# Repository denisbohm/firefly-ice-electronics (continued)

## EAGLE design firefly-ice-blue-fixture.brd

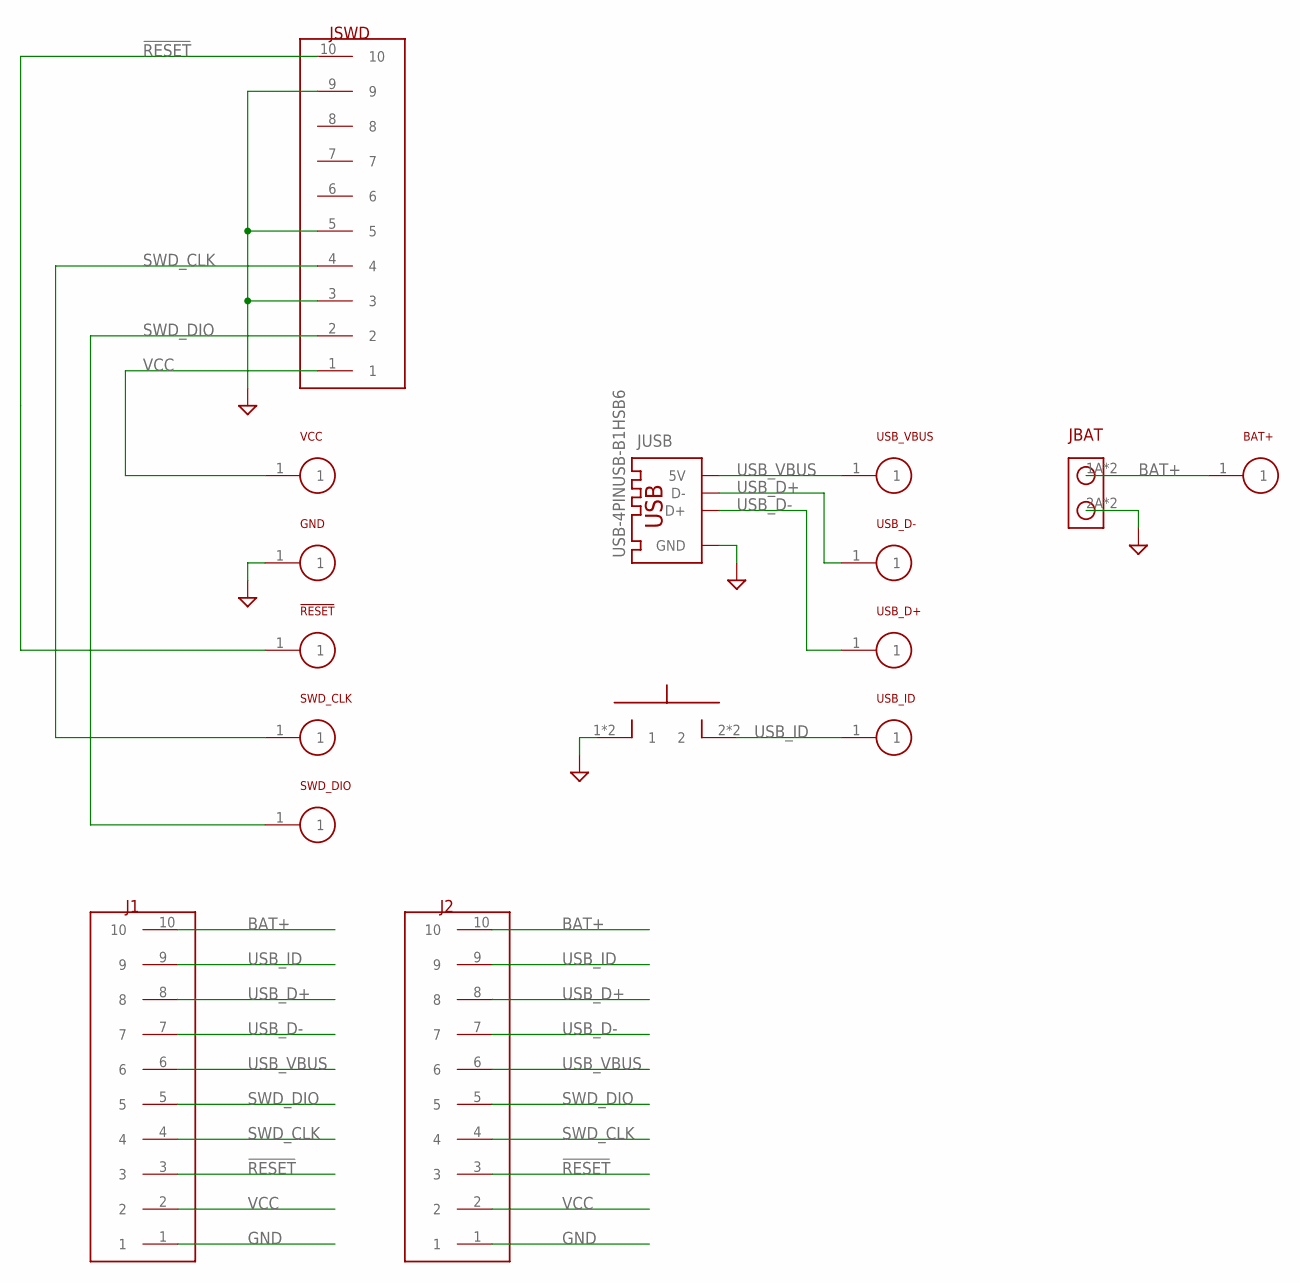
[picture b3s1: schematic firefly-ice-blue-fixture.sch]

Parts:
!RESET: TARGET-PINPROBE-0985; PROBE-0985
BAT+: TARGET-PINPROBE-0985; PROBE-0985
GND: TARGET-PINPROBE-0985; PROBE-0985
J1, J2: CON-10; CON-HEADER-10
JBAT: CON-220020303-D021B01LF; 20020303-D021B01LF
JSWD: CON-10SWD; SWD-10
JUSB: USB-4PINUSB-B1HSB6; USB-B1HSB6
SRES: SPST-NOKS-01Q-01; KS-01Q-01
SWD_CLK: TARGET-PINPROBE-0985; PROBE-0985
SWD_DIO: TARGET-PINPROBE-0985; PROBE-0985
USB_D+: TARGET-PINPROBE-0985; PROBE-0985
USB_D-: TARGET-PINPROBE-0985; PROBE-0985
USB_ID: TARGET-PINPROBE-0985; PROBE-0985
USB_VBUS: TARGET-PINPROBE-0985; PROBE-0985
VCC: TARGET-PINPROBE-0985; PROBE-0985

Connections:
!RESET: !RESET.1, J1.3, J2.3, JSWD.10
BAT+: BAT+.1, J1.10, J2.10, JBAT.1A (1), JBAT.1B (1)
GND: GND.1, J1.1, J2.1, JBAT.2A (2), JBAT.2B (2), JSWD.3, JSWD.5, JSWD.9, JUSB.4 (GND), SRES.1, SRES.3 (1)
SWD_CLK: J1.4, J2.4, JSWD.4, SWD_CLK.1
SWD_DIO: J1.5, J2.5, JSWD.2, SWD_DIO.1
USB_D+: J1.8, J2.8, JUSB.2 (D-), USB_D-.1
USB_D-: J1.7, J2.7, JUSB.3 (D+), USB_D+.1
USB_ID: J1.9, J2.9, SRES.2, SRES.4 (2), USB_ID.1
USB_VBUS: J1.6, J2.6, JUSB.1 (5V), USB_VBUS.1
VCC: J1.2, J2.2, JSWD.1, VCC.1

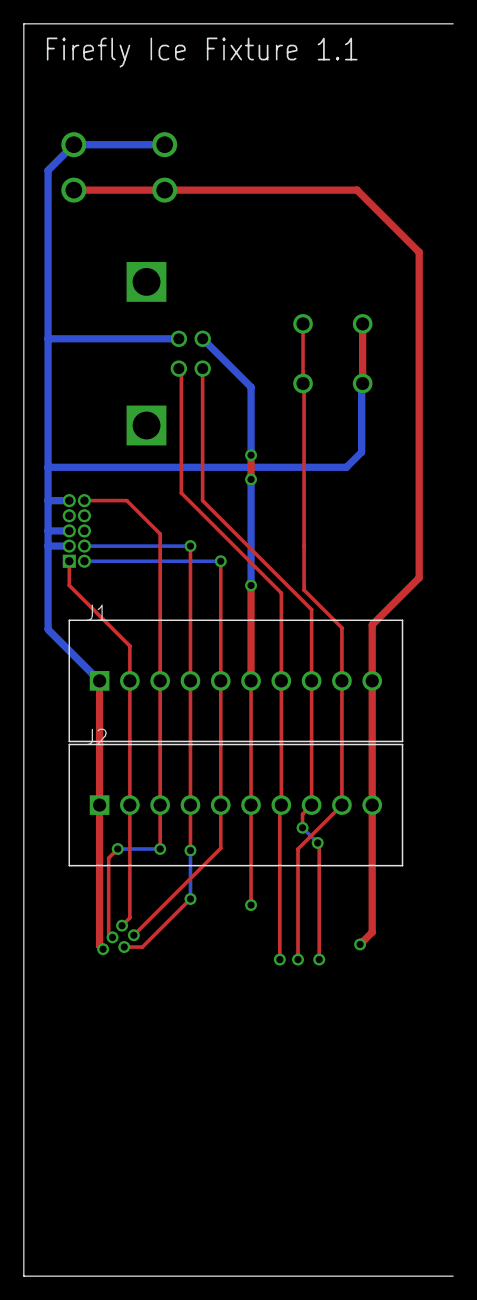
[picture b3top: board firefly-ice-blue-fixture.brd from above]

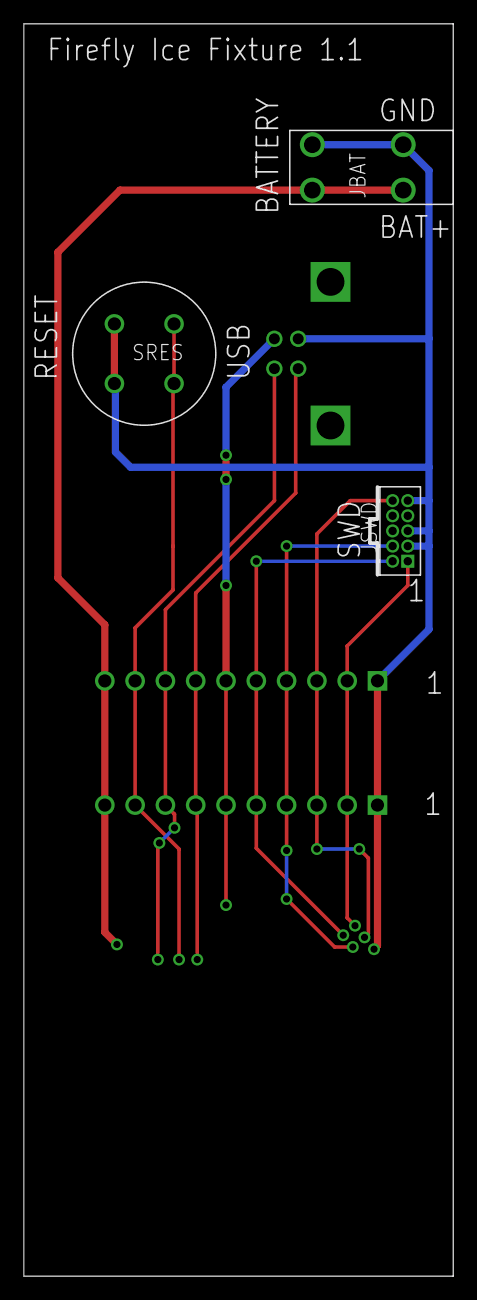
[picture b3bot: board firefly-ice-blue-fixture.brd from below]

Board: 2 copper layers, 36.0 x 105.0 mm, 16 parts (4 on the bottom side), 10 nets.

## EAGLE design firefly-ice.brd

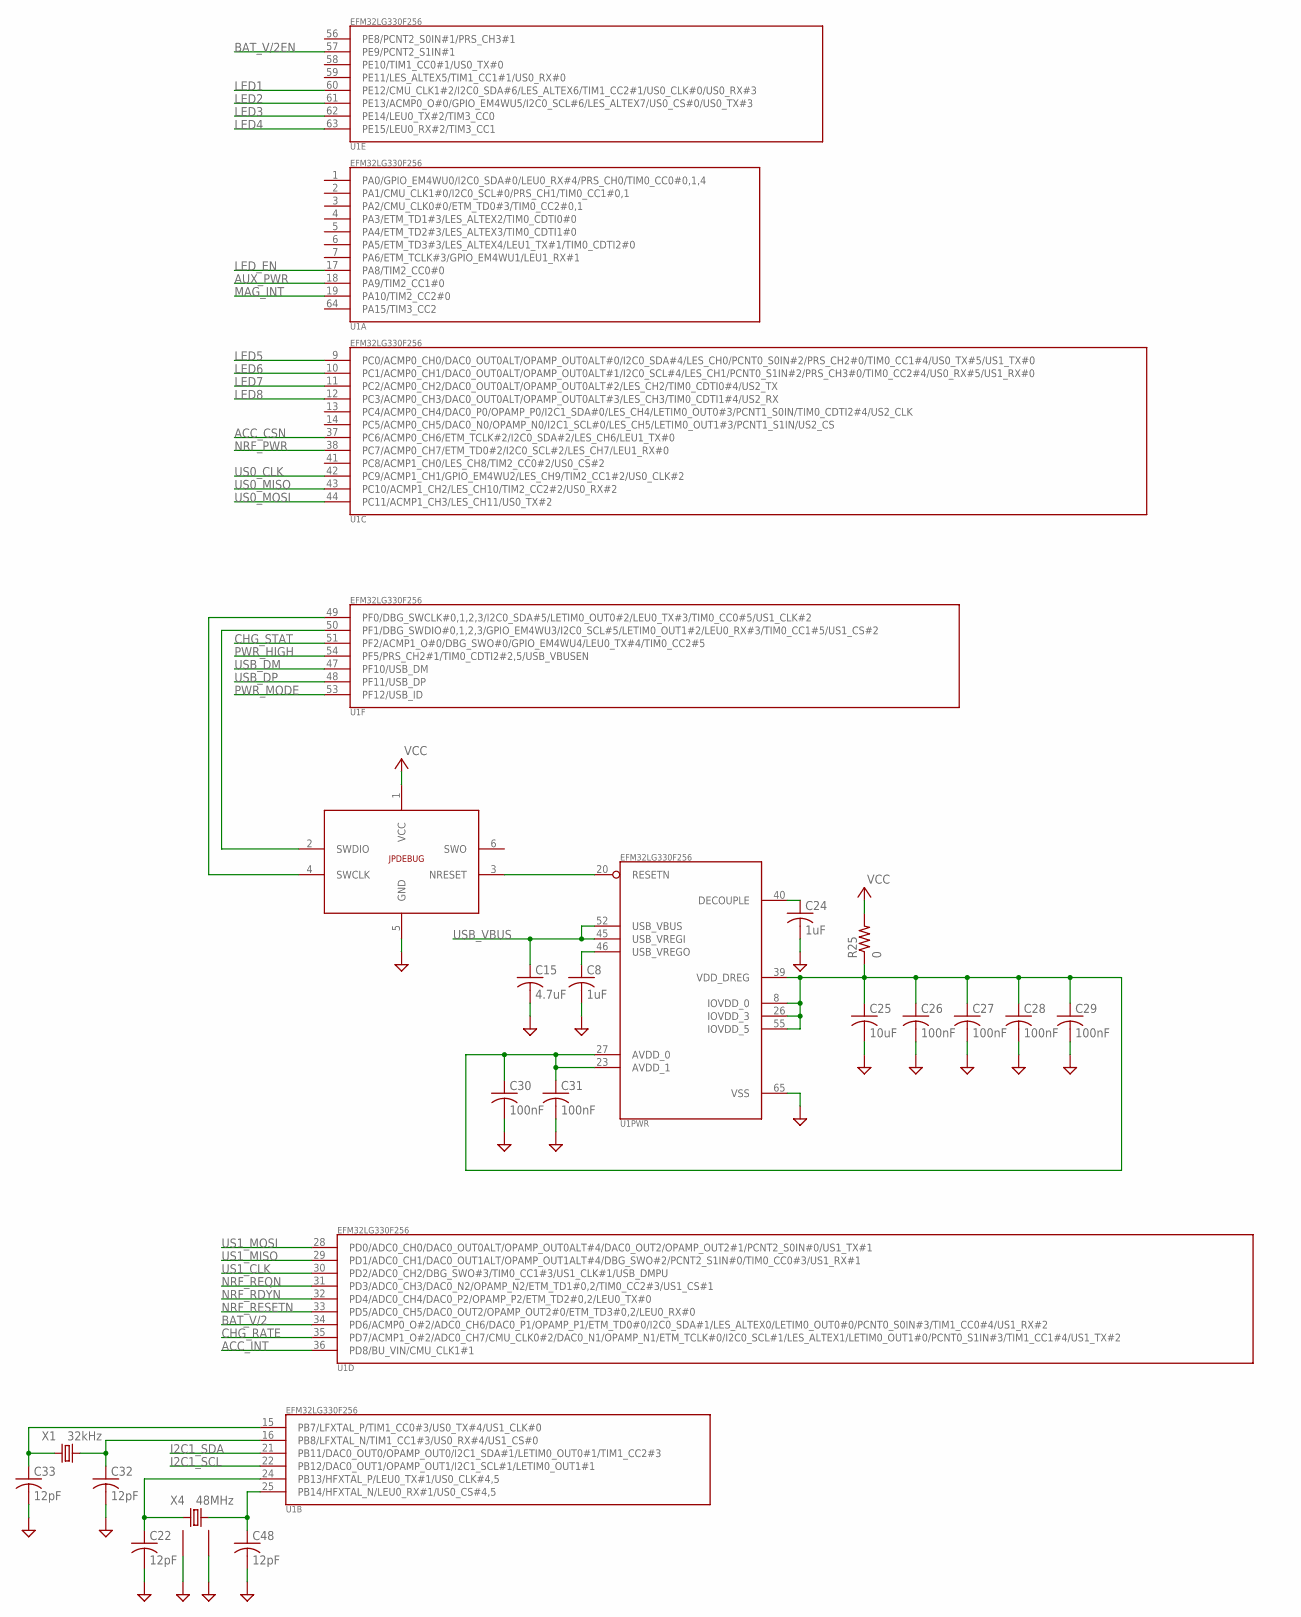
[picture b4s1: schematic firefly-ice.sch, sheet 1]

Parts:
C8, C24: 1uF; C0201
C15: 4.7uF; C0402
C22, C32, C33, C48: 12pF; C0201
C25: 10uF; C0402
C26, C27, C28, C29, C30, C31: 100nF; C0201
JPDEBUG: TC2030-SWD; TC2030-MCP-NL
R25: 0; R0603@1
U1: EFM32LG330F256; QFN64
X1: 32kHz; 9HT10
X4: 48MHz; ABM11

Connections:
ACC_CSN: U1.37 (PC6/ACMP0_CH6/ETM_TCLK#2/I2C0_SDA#2/LES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); also elsewhere on the board
ACC_INT: U1.36 (PD8/BU_VIN/CMU_CLK1#1); also elsewhere on the board
AUX_PWR: U1.18 (PA9/TIM2_CC1#0); also elsewhere on the board
BAT_V/2: U1.34 (PD6/ACMP0_O#2/ADC0_CH6/DAC0_P1/OPAMP_P1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); also elsewhere on the board
BAT_V/2EN: U1.57 (PE9/PCNT2_S1IN#1); also elsewhere on the board
CHG_RATE: U1.35 (PD7/ACMP1_O#2/ADC0_CH7/CMU_CLK0#2/DAC0_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); also elsewhere on the board
CHG_STAT: U1.51 (PF2/ACMP1_O#0/DBG_SWO#0/GPIO_EM4WU4/LEU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); also elsewhere on the board
GND: C8.2, C15.2, C22.2, C24.2, C25.2, C26.2, C27.2, C28.2, C29.2, C30.2, C31.2, C32.2, C33.2, C48.2, JPDEBUG.5 (GND), U1.65 (VSS), X4.2 (GND1), X4.4 (GND2); also elsewhere on the board
I2C1_SCL: U1.22 (PB12/DAC0_OUT1/OPAMP_OUT1/I2C1_SCL#1/LE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); also elsewhere on the board
I2C1_SDA: U1.21 (PB11/DAC0_OUT0/OPAMP_OUT0/I2C1_SDA#1/LE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); also elsewhere on the board
LED1: U1.60 (PE12/CMU_CLK1#2/I2C0_SDA#6/LES_ALTEX6/T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); also elsewhere on the board
LED2: U1.61 (PE13/ACMP0_O#0/GPIO_EM4WU5/I2C0_SCL#6/L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); also elsewhere on the board
LED3: U1.62 (PE14/LEU0_TX#2/TIM3_CC0); also elsewhere on the board
LED4: U1.63 (PE15/LEU0_RX#2/TIM3_CC1); also elsewhere on the board
LED5: U1.9 (PC0/ACMP0_CH0/DAC0_OUT0ALT/OPAMP_OUT0AL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); also elsewhere on the board
LED6: U1.10 (PC1/ACMP0_CH1/DAC0_OUT0ALT/OPAMP_OUT0AL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); also elsewhere on the board
LED7: U1.11 (PC2/ACMP0_CH2/DAC0_OUT0ALT/OPAMP_OUT0AL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); also elsewhere on the board
LED8: U1.12 (PC3/ACMP0_CH3/DAC0_OUT0ALT/OPAMP_OUT0AL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); also elsewhere on the board
LED_EN: U1.17 (PA8/TIM2_CC0#0); also elsewhere on the board
MAG_INT: U1.19 (PA10/TIM2_CC2#0); also elsewhere on the board
unnamed: JPDEBUG.3 (NRESET), U1.20 (RESETN)
unnamed: C8.1, U1.46 (USB_VREGO)
unnamed: C48.1, U1.25 (PB14/HFXTAL_N/LEU0_RX#1/US0_CS#4,5), X4.3 (2)
unnamed: C24.1, U1.40 (DECOUPLE)
unnamed: C33.1, U1.15 (PB7/LFXTAL_P/TIM1_CC0#3/US0_TX#4/US1_CL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), X1.1
unnamed: C22.1, U1.24 (PB13/HFXTAL_P/LEU0_TX#1/US0_CLK#4,5), X4.1
unnamed: JPDEBUG.2 (SWDIO), U1.50 (PF1/DBG_SWDIO#0,1,2,3/GPIO_EM4WU3/I2C0_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)
unnamed: JPDEBUG.4 (SWCLK), U1.49 (PF0/DBG_SWCLK#0,1,2,3/I2C0_SDA#5/LETIM0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)
unnamed: C32.1, U1.16 (PB8/LFXTAL_N/TIM1_CC1#3/US0_RX#4/US1_CS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), X1.2
unnamed: C25.1, C26.1, C27.1, C28.1, C29.1, C30.1, C31.1, R25.1, U1.8 (IOVDD_0), U1.23 (AVDD_1), U1.26 (IOVDD_3), U1.27 (AVDD_0), U1.39 (VDD_DREG), U1.55 (IOVDD_5)
NRF_PWR: U1.38 (PC7/ACMP0_CH7/ETM_TD0#2/I2C0_SCL#2/LES_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); also elsewhere on the board
NRF_RDYN: U1.32 (PD4/ADC0_CH4/DAC0_P2/OPAMP_P2/ETM_TD2#0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); also elsewhere on the board
NRF_REQN: U1.31 (PD3/ADC0_CH3/DAC0_N2/OPAMP_N2/ETM_TD1#0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); also elsewhere on the board
NRF_RESETN: U1.33 (PD5/ADC0_CH5/DAC0_OUT2/OPAMP_OUT2#0/ETM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); also elsewhere on the board
PWR_HIGH: U1.54 (PF5/PRS_CH2#1/TIM0_CDTI2#2,5/USB_VBUSEN); also elsewhere on the board
PWR_MODE: U1.53 (PF12/USB_ID); also elsewhere on the board
US0_CLK: U1.42 (PC9/ACMP1_CH1/GPIO_EM4WU2/LES_CH9/TIM2_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); also elsewhere on the board
US0_MISO: U1.43 (PC10/ACMP1_CH2/LES_CH10/TIM2_CC2#2/US0_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); also elsewhere on the board
US0_MOSI: U1.44 (PC11/ACMP1_CH3/LES_CH11/US0_TX#2); also elsewhere on the board
US1_CLK: U1.30 (PD2/ADC0_CH2/DBG_SWO#3/TIM0_CC1#3/US1_C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); also elsewhere on the board
US1_MISO: U1.29 (PD1/ADC0_CH1/DAC0_OUT1ALT/OPAMP_OUT1ALT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); also elsewhere on the board
US1_MOSI: U1.28 (PD0/ADC0_CH0/DAC0_OUT0ALT/OPAMP_OUT0ALT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); also elsewhere on the board
USB_DM: U1.47 (PF10/USB_DM); also elsewhere on the board
USB_DP: U1.48 (PF11/USB_DP); also elsewhere on the board
USB_VBUS: C15.1, U1.45 (USB_VREGI), U1.52 (USB_VBUS); also elsewhere on the board
VCC: JPDEBUG.1 (VCC), R25.2; also elsewhere on the board

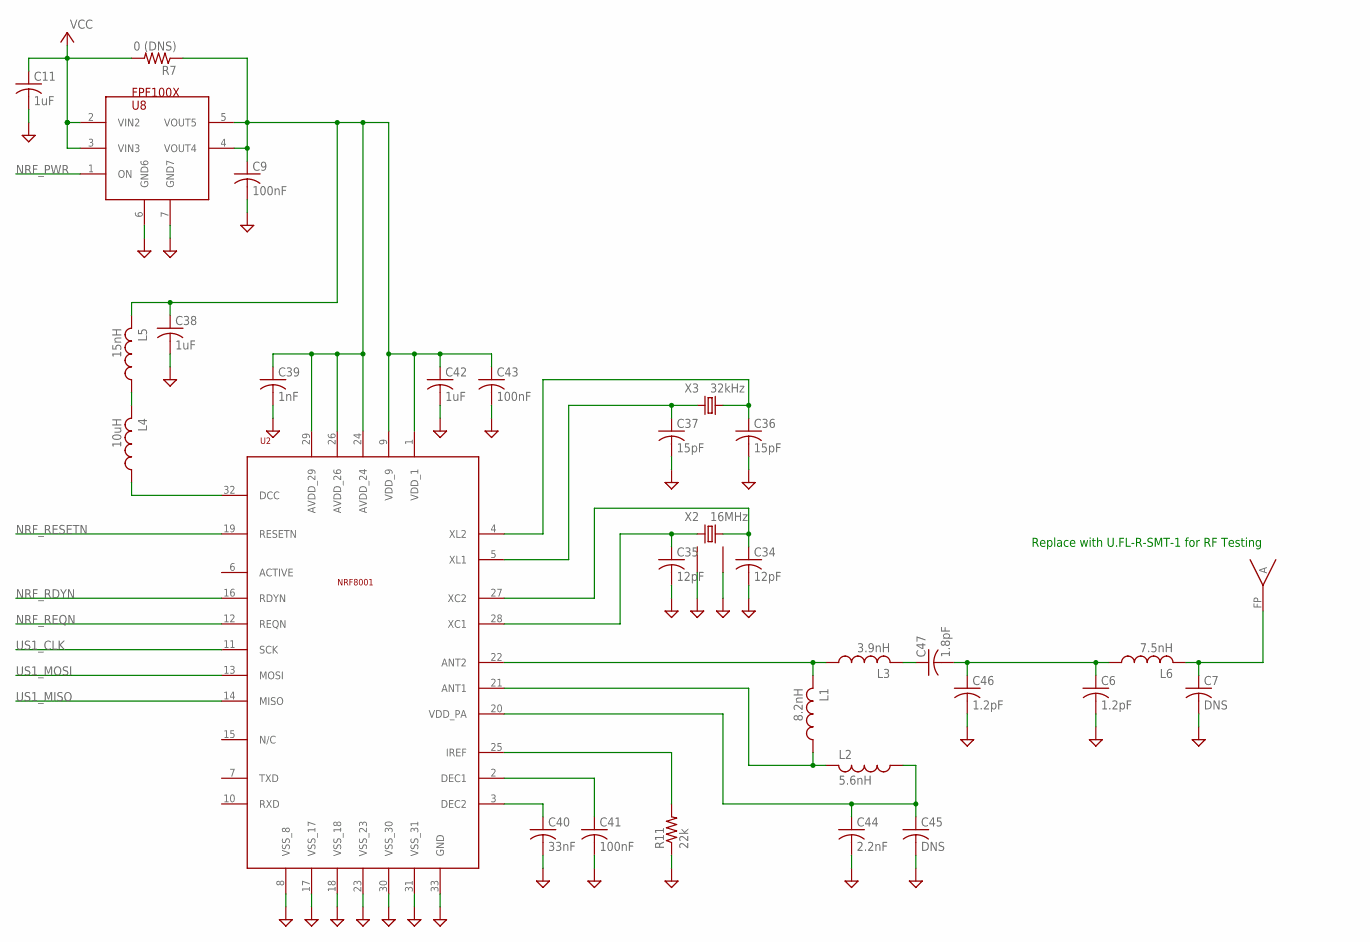
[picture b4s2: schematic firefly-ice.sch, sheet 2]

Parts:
A1: FR05_S1_N_0_110
C6, C46: 1.2pF; C0201
C7, C45: DNS; C0201
C9, C41, C43: 100nF; C0201
C11, C38, C42: 1uF; C0201
C34, C35: 12pF; C0201
C36, C37: 15pF; C0201
C39: 1nF; C0201
C40: 33nF; C0201
C44: 2.2nF; C0201
C47: 1.8pF; C0201
L1: 8.2nH; L0201
L2: 5.6nH; L0201
L3: 3.9nH; L0201
L4: 10uH; 0603
L5: 15nH; L0201
L6: 7.5nH; L0201
R7: 0 (DNS); R0201
R11: 22k; R0201
U2: NRF8001; QFN-32
U8: FPF100X; MICROFET-2X2-6L
X2: 16MHz; TSX-3225
X3: 32kHz; 9HT10

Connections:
GND: C6.2, C7.2, C9.2, C11.2, C34.2, C35.2, C36.2, C37.2, C38.2, C39.2, C40.2, C41.2, C42.2, C43.2, C44.2, C45.2, C46.2, R11.1, U2.8 (VSS_8), U2.17 (VSS_17), U2.18 (VSS_18), U2.23 (VSS_23), U2.30 (VSS_30), U2.31 (VSS_31), U2.33 (GND), U8.6 (GND6), U8.7 (GND7), X2.2 (GND1), X2.4 (GND2); also elsewhere on the board
unnamed: A1.FP, C7.1, L6.2
unnamed: C9.1, C38.1, C39.1, C42.1, C43.1, L5.2, R7.1, U2.1 (VDD_1), U2.9 (VDD_9), U2.24 (AVDD_24), U2.26 (AVDD_26), U2.29 (AVDD_29), U8.4 (VOUT4), U8.5 (VOUT5)
unnamed: C35.1, U2.28 (XC1), X2.1
unnamed: C34.1, U2.27 (XC2), X2.3 (2)
unnamed: C37.1, U2.5 (XL1), X3.1
unnamed: C36.1, U2.4 (XL2), X3.2
unnamed: R11.2, U2.25 (IREF)
unnamed: C40.1, U2.3 (DEC2)
unnamed: C41.1, U2.2 (DEC1)
unnamed: C47.1, L3.2
unnamed: C6.1, C46.1, C47.2, L6.1
unnamed: C44.1, C45.1, L2.1, U2.20 (VDD_PA)
unnamed: L1.1, L2.2, U2.21 (ANT1)
unnamed: L1.2, L3.1, U2.22 (ANT2)
unnamed: L4.1, U2.32 (DCC)
unnamed: L4.2, L5.1
NRF_PWR: U8.1 (ON); also elsewhere on the board
NRF_RDYN: U2.16 (RDYN); also elsewhere on the board
NRF_REQN: U2.12 (REQN); also elsewhere on the board
NRF_RESETN: U2.19 (RESETN); also elsewhere on the board
US1_CLK: U2.11 (SCK); also elsewhere on the board
US1_MISO: U2.14 (MISO); also elsewhere on the board
US1_MOSI: U2.13 (MOSI); also elsewhere on the board
VCC: C11.1, R7.2, U8.2 (VIN2), U8.3 (VIN3); also elsewhere on the board

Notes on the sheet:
Replace with U.FL-R-SMT-1 for RF Testing

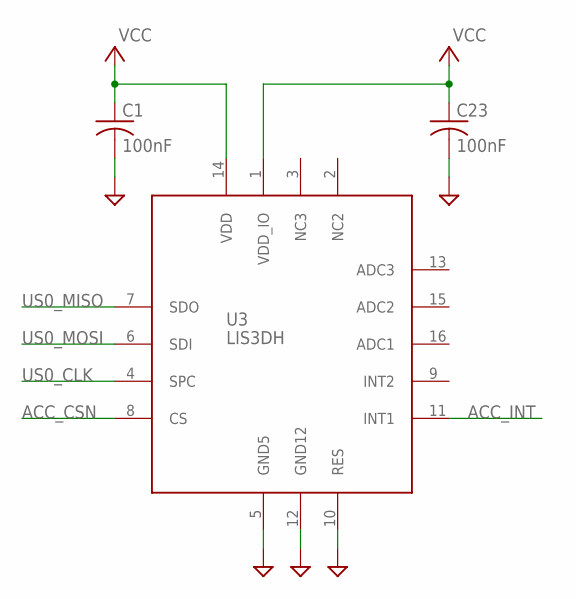
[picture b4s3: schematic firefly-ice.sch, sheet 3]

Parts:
C1, C23: 100nF; C0201
U3: LIS3DH; LGA16_3X3

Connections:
ACC_CSN: U3.8 (CS); also elsewhere on the board
ACC_INT: U3.11 (INT1); also elsewhere on the board
GND: C1.2, C23.2, U3.5 (GND5), U3.10 (RES), U3.12 (GND12); also elsewhere on the board
US0_CLK: U3.4 (SPC); also elsewhere on the board
US0_MISO: U3.7 (SDO); also elsewhere on the board
US0_MOSI: U3.6 (SDI); also elsewhere on the board
VCC: C1.1, C23.1, U3.1 (VDD_IO), U3.14 (VDD); also elsewhere on the board

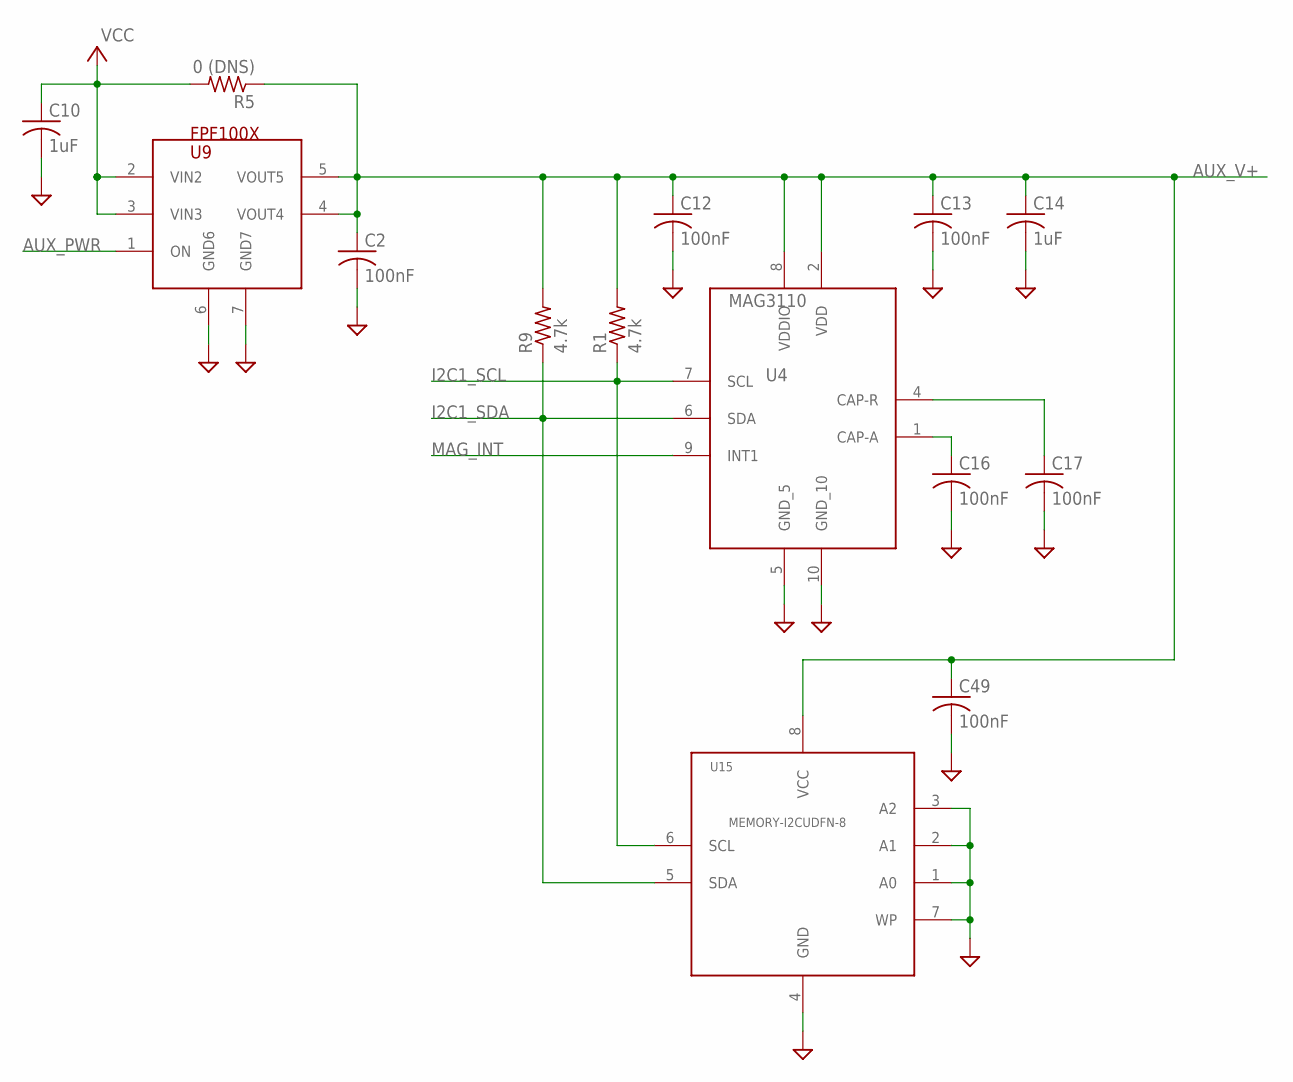
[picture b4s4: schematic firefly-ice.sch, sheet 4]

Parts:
C2, C12, C13, C16, C17, C49: 100nF; C0201
C10, C14: 1uF; C0201
R1, R9: 4.7k; R0201
R5: 0 (DNS); R0201
U4: MAG3110; DFN10-2X2
U9: FPF100X; MICROFET-2X2-6L
U15: MEMORY-I2CUDFN-8; UDFN-8

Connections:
AUX_PWR: U9.1 (ON); also elsewhere on the board
AUX_V+: C2.1, C12.1, C13.1, C14.1, C49.1, R1.2, R5.1, R9.2, U4.2 (VDD), U4.8 (VDDIO), U9.4 (VOUT4), U9.5 (VOUT5), U15.8 (VCC); also elsewhere on the board
GND: C2.2, C10.2, C12.2, C13.2, C14.2, C16.2, C17.2, C49.2, U4.5 (GND_5), U4.10 (GND_10), U9.6 (GND6), U9.7 (GND7), U15.1 (A0), U15.2 (A1), U15.3 (A2), U15.4 (GND), U15.7 (WP); also elsewhere on the board
I2C1_SCL: R1.1, U4.7 (SCL), U15.6 (SCL); also elsewhere on the board
I2C1_SDA: R9.1, U4.6 (SDA), U15.5 (SDA); also elsewhere on the board
MAG_INT: U4.9 (INT1); also elsewhere on the board
unnamed: C16.1, U4.1 (CAP-A)
unnamed: C17.1, U4.4 (CAP-R)
VCC: C10.1, R5.2, U9.2 (VIN2), U9.3 (VIN3); also elsewhere on the board

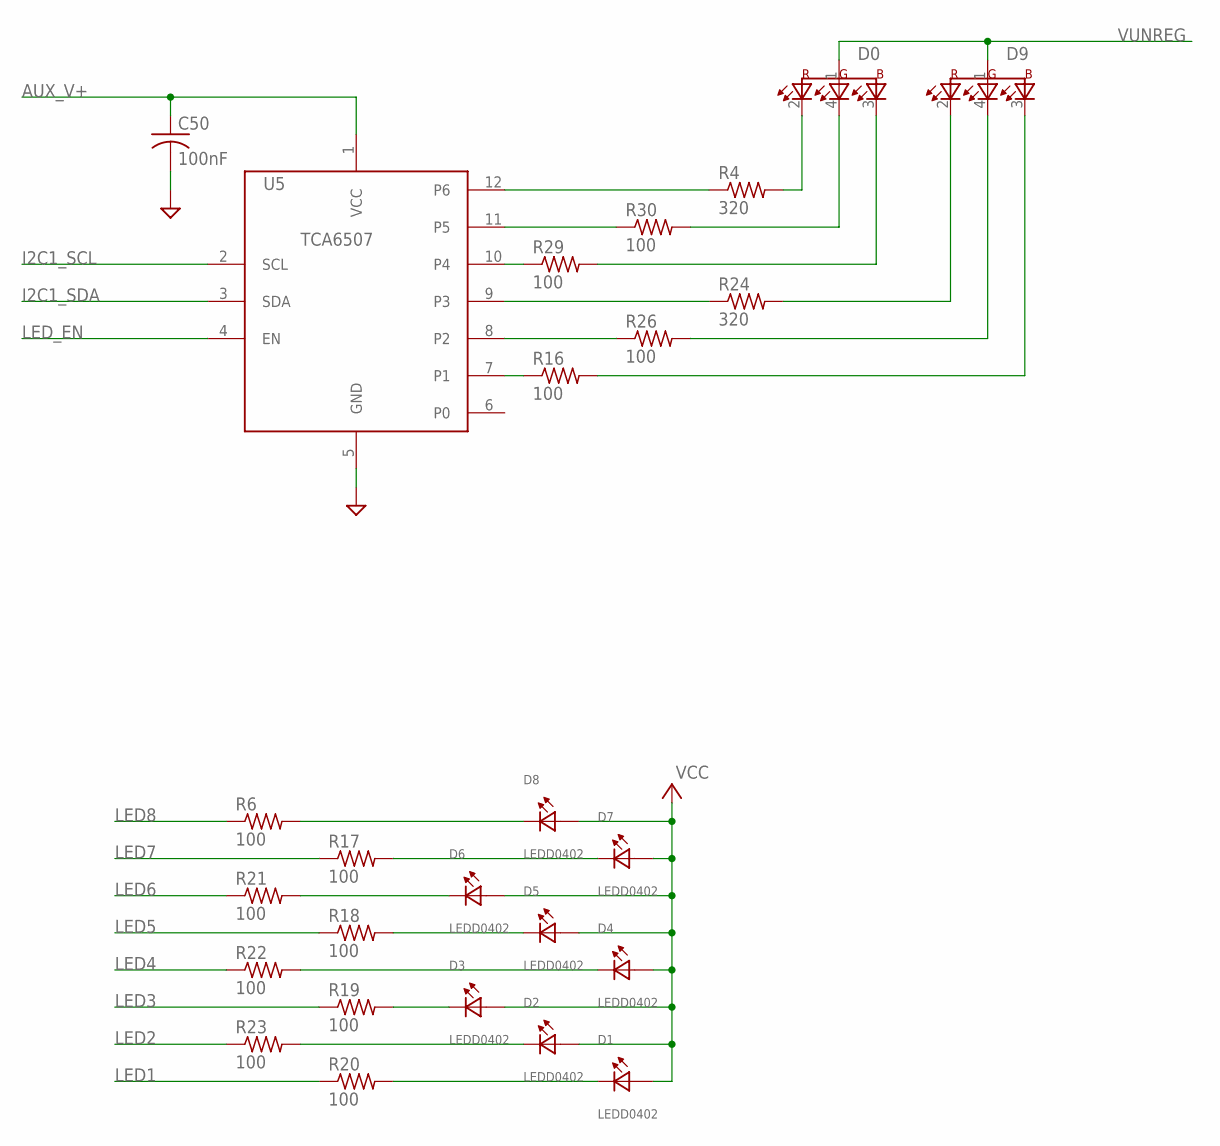
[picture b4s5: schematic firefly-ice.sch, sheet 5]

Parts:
C50: 100nF; C0201
D0, D9: LED-RGB-CASMLP34; SMLP34
D1, D2, D3, D4, D5, D6, D7, D8: LEDD0402; D0402
R4, R24: 320; R0201
R6, R16, R17, R18, R19, R20, R21, R22, R23, R26, R29, R30: 100; R0201
U5: TCA6507; R-PX2QFN-N12

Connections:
AUX_V+: C50.1, U5.1 (VCC); also elsewhere on the board
D0: D0.4 (G), R30.2
GND: C50.2, U5.5 (GND); also elsewhere on the board
I2C1_SCL: U5.2 (SCL); also elsewhere on the board
I2C1_SDA: U5.3 (SDA); also elsewhere on the board
LED1: R20.1; also elsewhere on the board
LED2: R23.1; also elsewhere on the board
LED3: R19.1; also elsewhere on the board
LED4: R22.1; also elsewhere on the board
LED5: R18.1; also elsewhere on the board
LED6: R21.1; also elsewhere on the board
LED7: R17.1; also elsewhere on the board
LED8: R6.1; also elsewhere on the board
LED_EN: U5.4 (EN); also elsewhere on the board
unnamed: R24.1, U5.9 (P3)
unnamed: R29.1, U5.10 (P4)
unnamed: D8.C, R6.2
unnamed: D7.C, R17.2
unnamed: D6.C, R21.2
unnamed: D5.C, R18.2
unnamed: D4.C, R22.2
unnamed: D3.C, R19.2
unnamed: D2.C, R23.2
unnamed: D1.C, R20.2
unnamed: R4.1, U5.12 (P6)
unnamed: R16.1, U5.7 (P1)
unnamed: R26.1, U5.8 (P2)
unnamed: R30.1, U5.11 (P5)
unnamed: D0.3 (B), R29.2
unnamed: D9.4 (G), R26.2
unnamed: D9.3 (B), R16.2
unnamed: D0.2 (R), R4.2
unnamed: D9.2 (R), R24.2
VCC: D1.A, D2.A, D3.A, D4.A, D5.A, D6.A, D7.A, D8.A; also elsewhere on the board
VUNREG: D0.1 (A), D9.1 (A); also elsewhere on the board

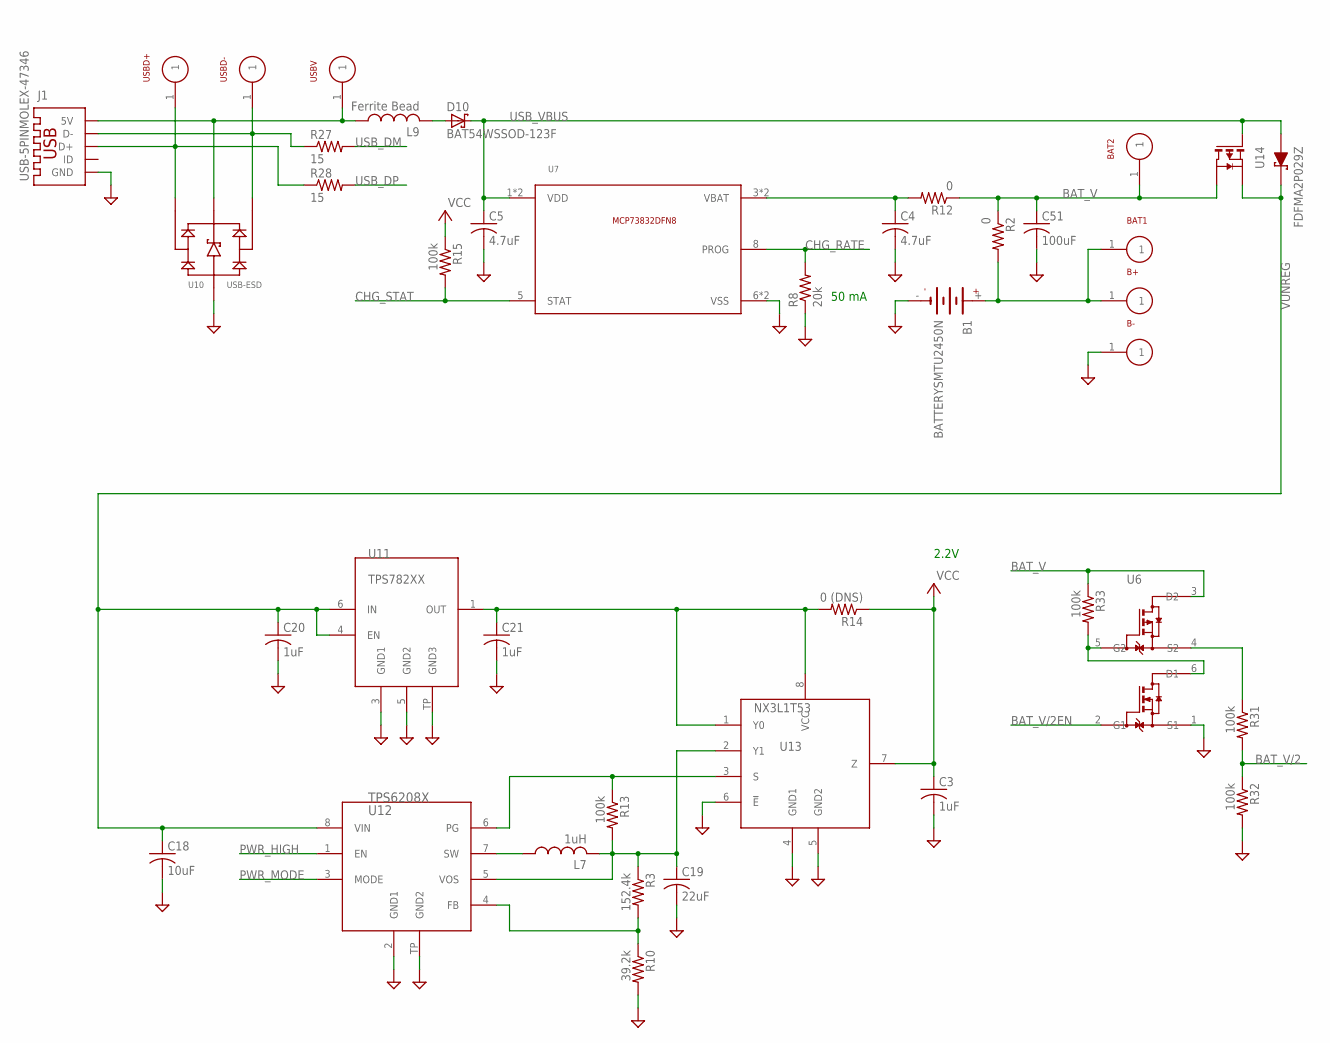
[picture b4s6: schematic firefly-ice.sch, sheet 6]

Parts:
B1: BATTERYSMTU2450N; SMTU2450N
B+: TARGET-PINWP-28AWG; WP-28AWG
B-: TARGET-PINWP-28AWG; WP-28AWG
BAT1, BAT2: TARGET-PIN; TARGET-PIN-1MM
C3, C20, C21: 1uF; C0201
C4, C5: 4.7uF; C0402
C18: 10uF; C0402
C19: 22uF; C0603
C51: 100uF; C1206
D10: BAT54WSSOD-123F; SOD-123F
J1: USB-5PINMOLEX-47346; MOLEX-47346
L7: 1uH; L0805
L9: Ferrite Bead; L0402
R2, R12: 0; R0603@1
R3: 152.4k; R0201
R8: 20k; R0201
R10: 39.2k; R0201
R13, R15, R31, R32, R33: 100k; R0201
R14: 0 (DNS); R0201
R27, R28: 15; R0201
U6: MOSFET-N+PSOT963; SOT963
U7: MCP73832DFN8; DFN8
U10: USB-ESD; UQFN6
U11: TPS782XX; S-PWSON-N6
U12: TPS6208X; S-PWSON-N8
U13: NX3L1T53; SOT902-2
U14: FDFMA2P029Z; MO-229
USBD+: TARGET-PIN; TARGET-PIN-1MM
USBD-: TARGET-PIN; TARGET-PIN-1MM
USBV: TARGET-PIN; TARGET-PIN-1MM

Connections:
BAT_V: BAT2.1, C51.1, R2.1, R12.1, R33.1, U6.3 (D2), U14.4 (S)
BAT_V/2: R31.2, R32.1; also elsewhere on the board
BAT_V/2EN: U6.2 (G1); also elsewhere on the board
CHG_RATE: R8.2, U7.8 (PROG); also elsewhere on the board
CHG_STAT: R15.2, U7.5 (STAT); also elsewhere on the board
GND: B1.-, B-.1, C3.2, C4.2, C5.2, C18.2, C19.2, C20.2, C21.2, C51.2, J1.5 (GND), J1.G1 (GND), J1.G2 (GND), J1.G3 (GND), J1.G4 (GND), J1.G5 (GND), J1.G6 (GND), R8.1, R10.2, R32.2, U6.1 (S1), U7.6 (VSS), U7.PGND (VSS), U10.2 (GND), U11.3 (GND1), U11.5 (GND2), U11.TP (GND3), U12.2 (GND1), U12.TP (GND2), U13.4 (GND1), U13.5 (GND2), U13.6 (!E); also elsewhere on the board
unnamed: C4.1, R12.2, U7.3 (VBAT), U7.4 (VBAT)
unnamed: R3.2, R10.1, U12.4 (FB)
unnamed: J1.3 (D+), R28.1, U10.1 (IO1), U10.6 (IO1), USBD+.1
unnamed: L7.1, U12.7 (SW)
unnamed: R13.1, U12.6 (PG), U13.3 (S)
unnamed: C19.1, L7.2, R3.1, R13.2, U12.5 (VOS), U13.2 (Y1)
unnamed: C21.1, R14.2, U11.1 (OUT), U13.1 (Y0), U13.8 (VCC)
unnamed: D10.A, L9.2
unnamed: J1.2 (D-), R27.1, U10.3 (IO2), U10.4 (IO2), USBD-.1
unnamed: J1.1 (5V), L9.1, U10.5 (VBUS), USBV.1
unnamed: R33.2, U6.5 (G2), U6.6 (D1)
unnamed: R31.1, U6.4 (S2)
PWR_HIGH: U12.1 (EN); also elsewhere on the board
PWR_MODE: U12.3 (MODE); also elsewhere on the board
USB_DM: R27.2; also elsewhere on the board
USB_DP: R28.2; also elsewhere on the board
USB_VBUS: C5.1, D10.C, U7.1 (VDD), U7.2 (VDD), U14.1 (A), U14.5 (G); also elsewhere on the board
VBATT: B1.+, B+.1, BAT1.1, R2.2
VCC: C3.1, R14.1, R15.1, U13.7 (Z); also elsewhere on the board
VUNREG: C18.1, C20.1, U11.4 (EN), U11.6 (IN), U12.8 (VIN), U14.3 (D), U14.6 (C), U14.C, U14.D; also elsewhere on the board

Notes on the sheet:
2.2V
50 mA

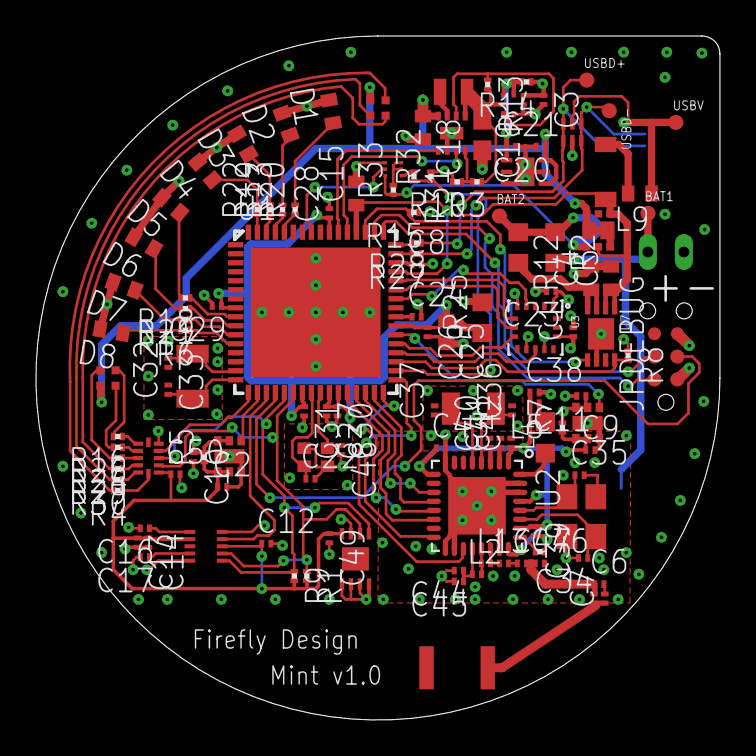
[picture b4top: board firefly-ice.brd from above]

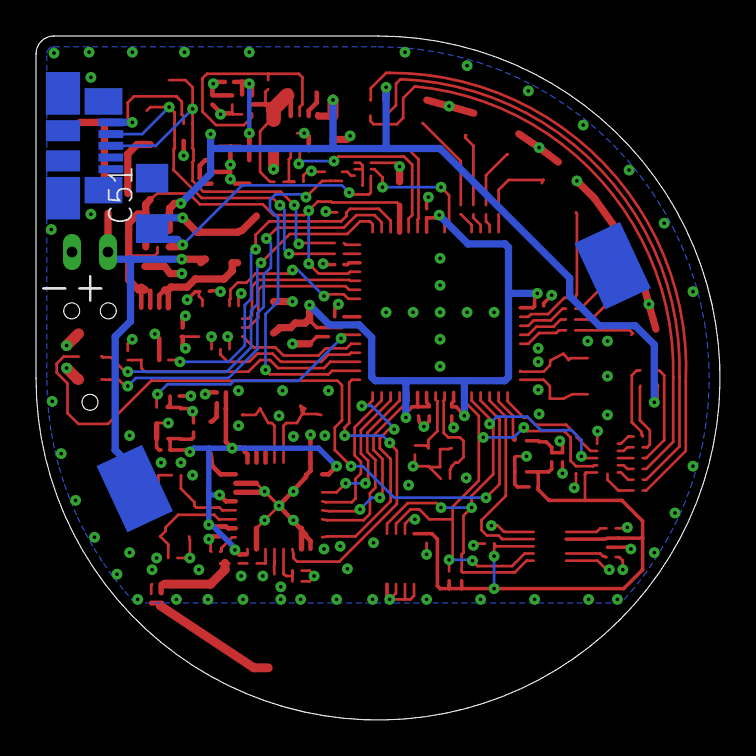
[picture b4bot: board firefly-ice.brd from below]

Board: 4 copper layers, 38.0 x 38.0 mm, 133 parts (3 on the bottom side), 100 nets.

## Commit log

2013-03-22 add link to blog
2013-03-22 initial version
2013-03-23 update URL
2013-03-24 update license info
2013-05-09 add pdf version of schematic
2013-06-01 second version of firefly ice: blue
2013-06-04 fix reversed source/drain on p-channel mosfet of voltage sensing circuit
2013-06-08 add schematic, bom, and assembly diagrams (derived from schematic and layout)
2013-07-13 switch to splashproof USB connector; fix voltage translator connections (swap A and B sides); DFM improvements
2013-07-29 add more part info for pricing
2013-09-03 fix power/ground short in USB connector mounting posts; fix MOSI/MISO to memory and add chip select pullup
2013-09-10 copy document layers so they can be used for silk names in panelized board
2014-01-06 add test fixture board
2014-02-05 increase size of test probe holes
2014-02-05 update license date
2014-02-05 add new derived files
2014-02-28 update license
2014-03-05 update some ordering codes
2014-03-05 move silk to component side of fixture PCB; remove old firefly ice
2014-04-27 raise voltage to 2.5V; make external usb id reset optional
2014-05-14 add accelerometer interrupt to pin 5 (since pin 4 can't be shared due to radio use)
2015-08-19 switch connector
2016-05-04 add instrument tray
2016-05-09 instrument tray ready to fab first version
2016-06-01 rev 0.2 of instrument board
2016-06-24 fix ordering codes on instrument board
2016-08-23 Firefly Instrument Tray 0.3 (out for fab)
2016-10-04 Rev 0.4 instrument board - ready for production
2016-10-19 fix SPI memory ordering code
2017-04-12 add battery simulator voltage to A/D; separate motor minus from ground; remove J2; bump to version 0.5
2017-04-13 revision 0.5 ready for production
